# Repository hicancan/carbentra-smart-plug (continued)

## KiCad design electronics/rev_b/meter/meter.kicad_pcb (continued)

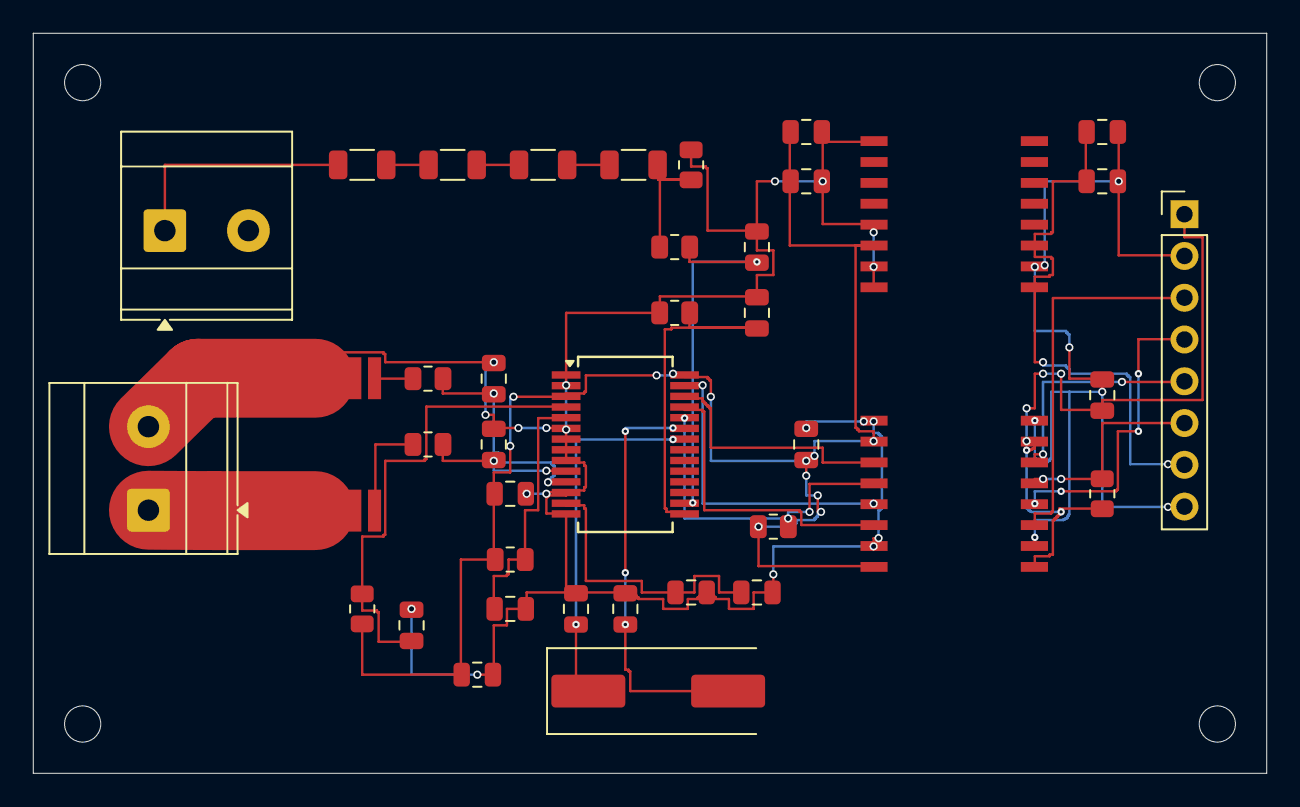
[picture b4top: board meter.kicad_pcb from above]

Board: 2 copper layers, 75.0 x 45.0 mm, 43 parts (0 on the bottom side), 30 nets.

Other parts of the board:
H1, H2, H3, H4: MountingHole_2.2mm_M2

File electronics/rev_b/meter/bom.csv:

Reference,Value,MPN candidate,Footprint,Source,Release
U1,ATM90E26-YU,ATM90E26-YU,Package_SO:SSOP-28_5.3x10.2mm_P0.65mm,https://ww1.microchip.com/downloads/aemDocuments/documents/O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,engineering candidate / hold
U2,ISO6741DWR,ISO6741DWR,RevB:ISO6741_DW_8p1,https://www.ti.com/lit/ds/symlink/iso6741.pdf,engineering candidate / hold
PS1,R05CT05S-R / 3.3V,R05CT05S-R,RevB:R05CT05S_8p1,https://recom-power.com/pdf/Econoline/RxxCTxx.pdf,engineering candidate / hold
RS1,1mR / 1% / 8W,CSS4J-4026R-1L00FE,RevB:CSS4J_4026,https://www.bourns.com/docs/product-datasheets/css4j-4026.pdf,engineering candidate / hold
J1,PROTECTED L / TO RELAY,1711725,TerminalBlock_Phoenix:TerminalBlock_Phoenix_MKDS-3-2-5.08_1x02_P5.08mm_Horizontal,https://www.phoenixcontact.com/en-pc/products/pcb-terminal-b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,engineering candidate / hold
J2,N SENSE / NC,1711725,TerminalBlock_Phoenix:TerminalBlock_Phoenix_MKDS-3-2-5.08_1x02_P5.08mm_Horizontal,https://www.phoenixcontact.com/en-pc/products/pcb-terminal-b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,engineering candidate / hold
J3,CONTROLLER - ISOLATED,TSW-108-07-G-S,Connector_PinHeader_2.54mm:PinHeader_1x08_P2.54mm_Vertical,https://www.samtec.com/products/tsw,engineering candidate / hold
R1,100R,TNPW0805100RBEEA,Resistor_SMD:R_0805_2012Metric,https://www.vishay.com/docs/28758/tnpw_e3.pdf,engineering candidate / hold
R2,100R,TNPW0805100RBEEA,Resistor_SMD:R_0805_2012Metric,https://www.vishay.com/docs/28758/tnpw_e3.pdf,engineering candidate / hold
C1,330nF 16V,GRM21-series 330nF 16V candidate,Capacitor_SMD:C_0805_2012Metric,https://www.murata.com/en-us/products/capacitor/ceramiccapacitor,engineering candidate / hold
C2,330nF 16V,GRM21-series 330nF 16V candidate,Capacitor_SMD:C_0805_2012Metric,https://www.murata.com/en-us/products/capacitor/ceramiccapacitor,engineering candidate / hold
RV1,249k,TNPW1206249KBEEA,Resistor_SMD:R_1206_3216Metric,https://www.vishay.com/docs/28758/tnpw_e3.pdf,engineering candidate / hold
RV2,249k,TNPW1206249KBEEA,Resistor_SMD:R_1206_3216Metric,https://www.vishay.com/docs/28758/tnpw_e3.pdf,engineering candidate / hold
RV3,249k,TNPW1206249KBEEA,Resistor_SMD:R_1206_3216Metric,https://www.vishay.com/docs/28758/tnpw_e3.pdf,engineering candidate / hold
RV4,249k,TNPW1206249KBEEA,Resistor_SMD:R_1206_3216Metric,https://www.vishay.com/docs/28758/tnpw_e3.pdf,engineering candidate / hold
RV5,1k,TNPW08051K00BEEA,Resistor_SMD:R_0805_2012Metric,https://www.vishay.com/docs/28758/tnpw_e3.pdf,engineering candidate / hold
RV6,1k,TNPW08051K00BEEA,Resistor_SMD:R_0805_2012Metric,https://www.vishay.com/docs/28758/tnpw_e3.pdf,engineering candidate / hold
RV7,1k,TNPW08051K00BEEA,Resistor_SMD:R_0805_2012Metric,https://www.vishay.com/docs/28758/tnpw_e3.pdf,engineering candidate / hold
CV1,33nF 16V,GRM21-series 33nF 16V candidate,Capacitor_SMD:C_0805_2012Metric,https://www.murata.com/en-us/products/capacitor/ceramiccapacitor,engineering candidate / hold
CV2,33nF 16V,GRM21-series 33nF 16V candidate,Capacitor_SMD:C_0805_2012Metric,https://www.murata.com/en-us/products/capacitor/ceramiccapacitor,engineering candidate / hold
R3,0R,RC0805JR-070RL,Resistor_SMD:R_0805_2012Metric,https://www.vishay.com/docs/28758/tnpw_e3.pdf,engineering candidate / hold
C3,100nF 16V,GRM21-series 100nF 16V candidate,Capacitor_SMD:C_0805_2012Metric,https://www.murata.com/en-us/products/capacitor/ceramiccapacitor,engineering candidate / hold
C4,100nF 16V,GRM21-series 100nF 16V candidate,Capacitor_SMD:C_0805_2012Metric,https://www.murata.com/en-us/products/capacitor/ceramiccapacitor,engineering candidate / hold
C5,10uF 10V,GRM21-series 10uF 10V candidate,Capacitor_SMD:C_0805_2012Metric,https://www.murata.com/en-us/products/capacitor/ceramiccapacitor,engineering candidate / hold
C6,1uF 16V,GRM21-series 1uF 16V candidate,Capacitor_SMD:C_0805_2012Metric,https://www.murata.com/en-us/products/capacitor/ceramiccapacitor,engineering candidate / hold
C7,1nF C0G,GRM21-series 1nF C0G candidate,Capacitor_SMD:C_0805_2012Metric,https://www.murata.com/en-us/products/capacitor/ceramiccapacitor,engineering candidate / hold
R4,10k,TNPW080510K0BEEA,Resistor_SMD:R_0805_2012Metric,https://www.vishay.com/docs/28758/tnpw_e3.pdf,engineering candidate / hold
C8,100nF 16V,GRM21-series 100nF 16V candidate,Capacitor_SMD:C_0805_2012Metric,https://www.murata.com/en-us/products/capacitor/ceramiccapacitor,engineering candidate / hold
Y1,8.192MHz CL18pF,ABLS-8.192MHZ-B2-T,Crystal:Crystal_SMD_HC49-SD,https://abracon.com/Resonators/abls.pdf,engineering candidate / hold
CX1,27pF C0G,GRM21-series 27pF C0G candidate,Capacitor_SMD:C_0805_2012Metric,https://www.murata.com/en-us/products/capacitor/ceramiccapacitor,engineering candidate / hold
CX2,27pF C0G,GRM21-series 27pF C0G candidate,Capacitor_SMD:C_0805_2012Metric,https://www.murata.com/en-us/products/capacitor/ceramiccapacitor,engineering candidate / hold
CP1,10uF 16V,GRM21-series 10uF 16V candidate,Capacitor_SMD:C_0805_2012Metric,https://www.murata.com/en-us/products/capacitor/ceramiccapacitor,engineering candidate / hold
CP2,100nF 16V,GRM21-series 100nF 16V candidate,Capacitor_SMD:C_0805_2012Metric,https://www.murata.com/en-us/products/capacitor/ceramiccapacitor,engineering candidate / hold
CP3,10uF 10V,GRM21-series 10uF 10V candidate,Capacitor_SMD:C_0805_2012Metric,https://www.murata.com/en-us/products/capacitor/ceramiccapacitor,engineering candidate / hold
CP4,100nF 16V,GRM21-series 100nF 16V candidate,Capacitor_SMD:C_0805_2012Metric,https://www.murata.com/en-us/products/capacitor/ceramiccapacitor,engineering candidate / hold
CI1,100nF 16V,GRM21-series 100nF 16V candidate,Capacitor_SMD:C_0805_2012Metric,https://www.murata.com/en-us/products/capacitor/ceramiccapacitor,engineering candidate / hold
CI2,100nF 16V,GRM21-series 100nF 16V candidate,Capacitor_SMD:C_0805_2012Metric,https://www.murata.com/en-us/products/capacitor/ceramiccapacitor,engineering candidate / hold
R5,10k,TNPW080510K0BEEA,Resistor_SMD:R_0805_2012Metric,https://www.vishay.com/docs/28758/tnpw_e3.pdf,engineering candidate / hold
R6,10k,TNPW080510K0BEEA,Resistor_SMD:R_0805_2012Metric,https://www.vishay.com/docs/28758/tnpw_e3.pdf,engineering candidate / hold

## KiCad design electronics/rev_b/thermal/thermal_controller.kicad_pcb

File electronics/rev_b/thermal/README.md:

# Rev B hardware thermal interlock: local rearm only

**ROUTED DEVELOPMENT CANDIDATES / FABRICATION AND ENERGIZATION HOLD.** The pin-connected circuit has separate 45 × 35 mm controller and 12 × 12 mm sensor-head PCBs, component footprints and a machine-readable manifest. These are digitally checked source boards, not a certified protective circuit or tested thermal assembly. EVT-A was not modified.

## Implemented behavior

The circuit adds independent hardware permission in series with the **5 V relay coil supply**. The existing MCU low-side relay driver still controls ordinary on/off operation, but cannot energize the coil while the thermal permission is cleared.

- Power-up and undervoltage clear the permission latch
- An overtemperature indication asynchronously clears it, regardless of clock/button state
- Cooling alone never rearms the latch
- A fresh **local physical rearm button** press is required after temperature is healthy and the supervisor settling interval finishes
- A button held through power-up, a fault or recovery does not create a fresh clock edge, and cannot automatically rearm after that recovery
- **There is no MCU or remote rearm net and no additional required MCU GPIO**
- Optional state observation is through TP1 (COIL_ARMED) and TP2 (THERMAL_READY), without a host GPIO dependency

This means **every power restoration requires a physical rearm press**. The finished product needs a qualified insulating actuator accessible with the enclosure closed, or it is a service-only arrangement. Opening a mains-connected enclosure to reach this prototype button is not an acceptable user workflow. This circuit does not provide the final button/enclosure safety design. A powered rearm could energize the coil immediately if the ordinary low-side RELAY_CMD is already HIGH; rearm is not a replacement for the system OFF command.

## Exact circuit

### 1. Sensor head

U1 is **TI TMP302BDRLR**, 6-pin SOT-563. Pin 5 takes +3V3_HEAD, pin 2 GND_HEAD, pins 1 and 6 are grounded for a provisional 70°C threshold, and pin 4 is high for 10°C hysteresis. Active-low pin 3 drives THERM_RETURN. R1 is a **10 kΩ pullup at the sensor head**, not at the controller; C1 is 100 nF across its supply. J4 is the sensor-side three-pad **front-SMD pigtail**, with 2.0 × 1.4 mm lands at 2.54 mm pitch and no through holes. The head is installed with its component face toward the rear. Pigtails and components occupy that rear-facing side; reserve 2 mm for wire/strain-relief assembly. The opposite, contact-facing B.Cu side has a fixed **GND_HEAD copper island** bounded by KiCad x=1.2…4.5 mm, y=4.3…6.9 mm, and four 0.3 mm drill / 0.6 mm copper thermal vias at (1.6,4.7), (2.4,4.7), (3.4,4.7), (4.2,4.7). These vias are tented in the source. No live-metal or separate isolated island is introduced. Smoothness, any via-fill/cap requirement, insulating thermal pad, pressure, wire anchoring and thermal lag remain unqualified. The part accuracy is ±2°C, but thermal coupling to the actual socket-contact hot spot is unqualified. [TI TMP302 pin table and configuration](https://www.ti.com/lit/gpn/TMP302)

At the controller, R2 = 100 kΩ pulls THERM_RETURN to GND_ISO; U2, **SN74LVC1G17DBVR**, restores it through a Schmitt buffer. Thus opening the return wire lets the controller input fall LOW. The normal healthy head pullup drives it HIGH. U2's output HEALTH_VALID drives U3 MR. The buffer prevents U3's internal MR pullup from defeating the return-wire pulldown.

**Coverage is limited:** return-wire open, head supply-wire open, and a return short to ground are intended to trip. A disconnected sensor ground, a return short to the supply, an internal sensor stuck-HIGH failure or some connector bridges may look healthy. This is not a fully supervised safety sensor loop. W1 and W2 are schematic-only harness conductor models, not BOM resistors.

### 2. Voltage supervision and settling

U3 is **TPS3808G30DBVR**, not G33. SOT-23-6 pin map: 1 RESET_N, 2 GND, 3 MR, 4 CT, 5 SENSE, 6 VDD. VDD and SENSE connect to isolated 3.3 V. HEALTH_VALID drives MR. R3 = 100 kΩ connects CT to VDD, selecting the manufacturer's **180–420 ms** specified delay. R4 = 10 kΩ pulls RESET_N high on READY_RAW. U6, SN74LVC1G17DBVR, buffers READY_RAW to THERMAL_READY with a fast Schmitt-trigger edge and local 100 nF bypass C7. This avoids presenting a slow open-drain RC rising edge directly to the flip-flop CLEAR input. LOW means not ready.

The G30 nominal falling threshold is 2.79 V. Including ±1.5% threshold accuracy and 2.5% maximum hysteresis gives a conservative release ceiling of **2.9016 V**, below the assumed 3.3 V −5% = 3.135 V rail. G33 can require more than 3.135 V at the upper threshold/hysteresis corner, so it was rejected for this rail assumption. The minimum 180 ms delay exceeds the sensor's 35 ms startup interval by 145 ms. [TI TPS3808 datasheet, G30 threshold, pin table and delay specifications](https://www.ti.com/lit/ds/symlink/tps3808.pdf)

A thermal fault drives MR LOW and asserts RESET_N without waiting for the release timer. Any fault during a pending settling period restarts the delay. The delay controls when rearming becomes possible; it does not itself energize the relay.

### 3. Trip-dominant latch

U4 is **SN74LVC1G74DCUR**, VSSOP-8:

| Pin | Connection |
|---|---|
| 1 CLK | REARM_CLK from U5 |
| 2 D | +3V3_ISO |
| 3 Q_N | no connection |
| 4 GND | GND_ISO |
| 5 Q | COIL_ARMED |
| 6 CLR_N | THERMAL_READY |
| 7 PRE_N | +3V3_ISO, permanently inactive |
| 8 VCC | +3V3_ISO |

The asynchronous CLEAR is the only asynchronous state-changing input in use. This avoids an SR latch's forbidden simultaneous set/reset combination. While CLEAR is LOW, Q is LOW even if the button generates clock edges. With CLEAR HIGH, a rising clock edge captures D = HIGH; otherwise the prior state is retained. A live fault also physically disables the series transistor gate independently of Q. [TI flip-flop datasheet and truth table](https://www.ti.com/lit/ds/symlink/sn74lvc1g74.pdf)

SW1, Omron B3F-1000, is the only rearm input. R5 = 1 kΩ limits charge into C5 = 100 nF; R7 = 100 kΩ discharges the node. U5, another SN74LVC1G17DBVR, converts the RC level to a clean clock transition. Pressed RC time constant is about 0.099 ms and released time constant is 10 ms. This is edge conditioning, not a certified debounce algorithm; repeated bounce clocks after a valid press merely capture the same HIGH. Release the button for at least 50 ms before a new deliberate press.

**Do not AND the clock with THERMAL_READY.** That would create a clock edge when a fault clears while the button is held, causing automatic rearm. The implemented circuit gates the asynchronous clear and the coil feed instead. The digital model tests that distinction.

### 4. Physical coil-feed interlock

Q1 is **AO3401A P-channel MOSFET**: pin 2 source to +5V_ISO, pin 3 drain to COIL_5V, pin 1 gate to COIL_GATE. R9 = 47 kΩ pulls its gate back to its source, the default OFF condition.

Q2 and Q3 are **Nexperia MMBT3904,215** NPNs, pin 1 base, pin 2 emitter, pin 3 collector. They form a series gate sink:

COIL_GATE → Q2 collector; Q2 emitter → Q3 collector; Q3 emitter → GND_ISO

Q2 base is driven by COIL_ARMED through 10 kΩ with a 100 kΩ base-emitter resistor. Q3 base is driven by THERMAL_READY through 47 kΩ with a 100 kΩ base-emitter resistor. Both stages must conduct to pull the PMOS gate low. Therefore forcing/sticking the logic latch Q HIGH does not bypass an actively LOW thermal/power-ready signal in the ideal functional model. [AO3401A datasheet](https://www.aosmd.com/res/data_sheets/AO3401A.pdf), [MMBT3904 datasheet](https://assets.nexperia.com/documents/data-sheet/MMBT3904.pdf)

Assume coil load ≤150 mA and +5 V ±5% for this candidate. Q1's 85 mΩ maximum specified at VGS = −2.5 V gives only 12.75 mV drop and 1.913 mW dissipation at 150 mA, at the specified test temperature; hot RDS(on), actual gate swing and release transients still need testing. The gate sink only needs ≤5.25/46.53 kΩ = **112.8 µA** steady-state. These are coil-driver calculations, not socket-load-current ratings.

**Integration change is mandatory:** J1.4 (COIL_5V) replaces the relay coil's old +5 V feed. The coil flyback diode's cathode must also connect to COIL_5V, with its anode at the existing low-side coil node. Otherwise the original wiring may bypass the intended current-decay loop or couple transients into the ungated rail. The existing low-side RELAY_CMD path remains. No load-current conductor is connected to this interlock PCB.

## Source and interfaces

- `thermal_interlock.kicad_sch`, `.kicad_pro`, `Thermal.kicad_sym`, `sym-lib-table`: KiCad source with embedded symbols
- `pin_net_manifest.json`: exact pins/nets, expected package footprints, normal supply/load assumptions
- `bom.csv`: component candidates; W1/W2 wire models excluded
- `exports/thermal.net`: actual KiCad-exported netlist
- `exports/thermal_interlock.svg` and `.png`: review drawing
- `scripts/build_thermal.py`: deterministic source rebuild
- `thermal_controller.kicad_pcb` / `thermal_sensor.kicad_pcb`: routed low-voltage PCB candidates
- `scripts/build_boards.py` and `routing_recipe.py`: physical source generation and deterministic replay of verified controller copper; `controller_route_recipe.json` is the checked routing source. The search/cleanup scripts are retained only as development tools
- `scripts/verify_thermal.py`: 94 schematic pins, both PCB pin maps, 13 ideal logic tests and DC calculations
- `scripts/rebuild.sh`: complete build/check sequence; fails if final digital verification fails

The four-wire host connection is J1.1 +5V_ISO, J1.2 +3V3_ISO, J1.3 GND_ISO, J1.4 COIL_5V. These map respectively to main controller J3 pins 7, 1, 11 and 10. There is no separate coil-feed connector. Sensor harness: 3V3, GND, THERM_RETURN. TP1 and TP2 are test points only. All electrical connections here are in the isolated low-voltage domain; maintaining isolation from mains at the remote sensor's thermal mounting is a separate mechanical/material requirement.

The routed board outlines are **45 × 35 × 1.6 mm controller** and **12 × 12 × 1.6 mm sensor head**. Reserve 9 mm above / 3 mm below the controller PCB for headers and tails, plus mating/bend space and reset-actuator clearance. The remote head uses **component-side SMD pigtails**: in the CAD local frame reserve **2 mm on the component side** and a provisional **0.1 mm copper/mask surface allowance on the opposite contact side**, then rotate the head 180° about local Y for the proposed installation. No solder or wire protrusion is permitted on the contact side. C1 is 0.9 mm high and U1 0.6 mm high, both facing the rear; the head must not be modeled as a bare 0.6 mm package. The captive insulating pad and supporting fixture bear on the smooth PCB backside, not the sensor case. Process qualification is still required. `exports/*_envelope.step`, `.FCStd` and `*_envelopes.json` provide simplified source-based package envelopes, not detailed vendor solids or completed enclosure-fit evidence. The neighboring `feedback/` module is a separate routed PCB.

## Checks and limits

Final checks show ERC 0 errors/warnings and DRC 0 violations / 0 unconnected pads on both boards. The controller contains 29 footprints and the head 4; all 94 logical pins match the schematic/manifest, with duplicate switch pads checked separately. The physical rules explicitly permit 0.15 mm isolated-LV fine-pitch clearance. No mains may be brought onto either thermal board. Independent checks compare the exported netlist to every manifest pin, separately assert the manufacturer-critical U3/U4/Q1 pin maps, and verify that no MCU rearm net remains. The ideal state tests include startup, held button, hot reset attempts, simultaneous fault/reset, brownout, repeated settling interruption, return-open fault input, stale-high Q, and preserved dependence on ordinary RELAY_CMD.

The DC calculations also include input leakage: the healthy sensor return is at least approximately **2.799 V** under the selected 3.3 V/resistor/input-leakage assumptions; an opened return stays at or below **0.505 V** with 5 µA worst input leakage. READY_RAW remains at least 3.0845 V with 5 µA buffer input leakage. U6 drives THERMAL_READY; its 100 µA output-load specification gives VOH ≥ VCC −0.1 V, while the connected base-resistor and CLEAR loads stay below that current under the stated assumptions. These values depend on the assumed input leakage, clean PCB and correct harness. They are not test evidence for fault coverage of an arbitrary cable or contaminated assembly.

### Power-up qualification is still open

The intended power-up state is OFF, and digital behavior after the parts enter their specified supply range is checked. **No analog supply-ramp test or transistor/SPICE simulation has established a guaranteed absence of a brief coil pulse at every sub-threshold voltage or supply ordering.** TPS3808's low-voltage reset guarantee depends on pullup loading and ramp conditions; do not extend its 15 µA VPOR test to this 10 kΩ pullup without measurement. Test +5 V first, 3.3 V first, slow/non-monotonic 3.3 V, brownouts, temperature corners and button held through all of them. The source is not released until default-OFF is verified at the actual coil/driver for these cases. Also qualify flip-flop clear recovery timing, RC bounce near the ready transition and the actual hot/cold Schmitt thresholds.

Other holds: physical board/assembly/EMC qualification; sensor thermal contact and insulation; actual relay inrush/hold/release characteristics; power-loss decay; transistor leakage and single faults; reset actuator access; harness open/short combinations; R/C drift; protection of the supply and wiring; fault response at the actual hottest socket/terminal. A shorted Q1 or some sensing faults can defeat this single-channel circuit. It is not a safety-certified or single-fault-tolerant channel.

## Physical thermal cutoff remains separate

A coil-feed interlock **cannot open welded load contacts**. Retain a separately thermally coupled, qualified series thermal cutoff in the load-line path. The neighboring feedback report identifies the MICROTEMP G5 family and provisional Tf98°C selection for supplier/load/thermal validation. No exact regional certification, lifetime or fuse coordination is claimed here. Even a thermal cutoff only interrupts after its thermal trigger is reached; guaranteed disconnection on a cold welded relay requires an independent rated interruption mechanism. PE remains continuous and unswitched.

## Proposed mechanics transform

TMP302 center is KiCad (3.4,6.0) mm on the 12×12 board, or (−2.6,0) relative to board center. A 180° local-Y rotation maps that to (+2.6,0). Therefore a board center at global (−16.6,−7) gives sensor center (−14,−7). With the contact-facing PCB backside at z=43.5 mm, the component face is z=41.9 mm and parts/wires extend rearward from there. This transform confirms geometry only, not measured coupling or electrical insulation.

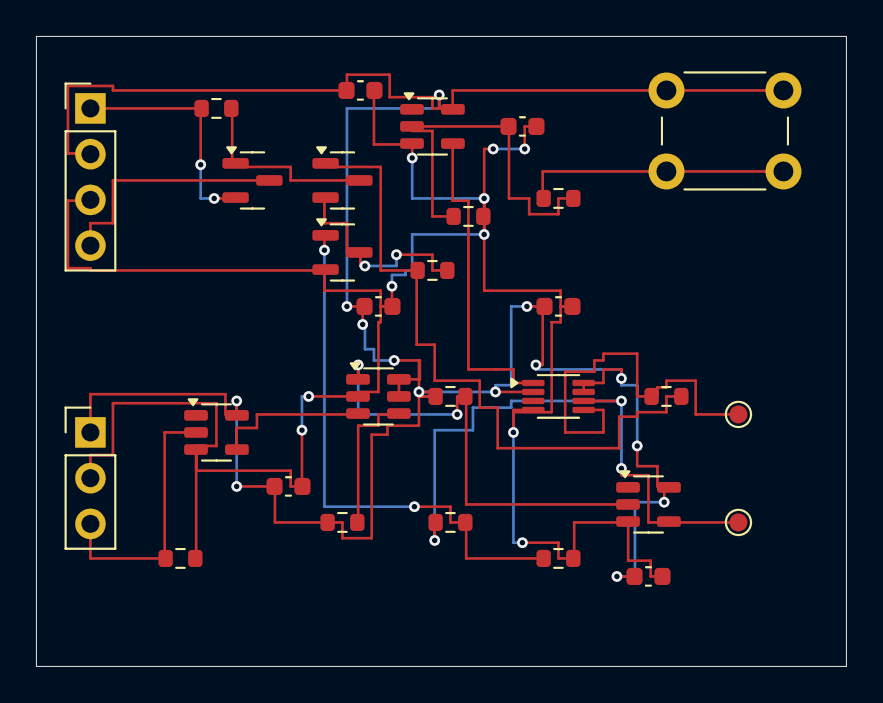
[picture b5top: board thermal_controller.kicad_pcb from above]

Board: 2 copper layers, 45.0 x 35.0 mm, 29 parts (0 on the bottom side), 17 nets.

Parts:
C2, C3, C4, C5, C6, C7: 100nF 16V X7R; C_0603_1608Metric
J1: MAIN 4-WIRE COIL INTERLOCK; PinHeader_1x04_P2.54mm_Vertical
J3: SENSOR HARNESS; PinHeader_1x03_P2.54mm_Vertical
Q1: AO3401A; SOT-23
Q2, Q3: MMBT3904; SOT-23
R2, R3, R7, R11, R13: 100k 1%; R_0603_1608Metric
R4, R10: 10k 1%; R_0603_1608Metric
R5: 1k 1%; R_0603_1608Metric
R9, R12: 47k 1%; R_0603_1608Metric
SW1: MANUAL REARM; SW_PUSH_6mm
TP1: COIL_ARMED; TestPoint_Pad_D1.0mm
TP2: THERMAL_READY; TestPoint_Pad_D1.0mm
U2, U5, U6: SN74LVC1G17DBVR; SOT-23-5
U3: TPS3808G30DBVR; SOT-23-6
U4: SN74LVC1G74DCUR; VSSOP-8_2.3x2mm_P0.5mm

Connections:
+3V3_ISO: C2.1, C3.1, C4.1, C6.1, C7.1, J1.2, J3.1, R3.1, R4.1, SW1.1, U2.5, U3.5, U3.6, U4.2, U4.7, U4.8, U5.5, U6.5
+5V_ISO: J1.1, Q1.2, R9.1
ARM_B: Q2.1, R10.2, R11.1
COIL_5V: J1.4, Q1.3
COIL_ARMED: R10.1, TP1.1, U4.5
COIL_GATE: Q1.1, Q2.3, R9.2
CT_SELECT: R3.2, U3.4
GND_ISO: C2.2, C3.2, C4.2, C5.2, C6.2, C7.2, J1.3, J3.2, Q3.2, R2.2, R7.2, R13.2, U2.3, U3.2, U4.4, U5.3, U6.3
HEALTH_VALID: U2.4, U3.3
MANUAL_RAW: R5.1, SW1.2
READY_B: Q3.1, R12.2, R13.1
READY_RAW: R4.2, U3.1, U6.2
REARM_CLK: U4.1, U5.4
REARM_RC: C5.1, R5.2, R7.1, U5.2
SINK_MID: Q2.2, Q3.3, R11.2
THERMAL_READY: R12.1, TP2.1, U4.6, U6.4
THERM_RETURN: J3.3, R2.1, U2.2

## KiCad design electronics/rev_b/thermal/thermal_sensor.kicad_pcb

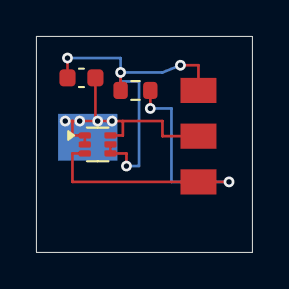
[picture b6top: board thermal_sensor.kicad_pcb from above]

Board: 2 copper layers, 12.0 x 12.0 mm, 4 parts (0 on the bottom side), 3 nets.

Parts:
C1: 100nF 16V X7R; C_0603_1608Metric
J4: SENSOR PIGTAIL; Sensor_Pigtail_3xP2.54
R1: 10k 1%; R_0603_1608Metric
U1: TMP302BDRLR; SOT-563

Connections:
+3V3_HEAD: C1.1, J4.1, R1.1, U1.4, U1.5
GND_HEAD: C1.2, J4.2, U1.1, U1.2, U1.6
THERM_RETURN: J4.3, R1.2, U1.3
